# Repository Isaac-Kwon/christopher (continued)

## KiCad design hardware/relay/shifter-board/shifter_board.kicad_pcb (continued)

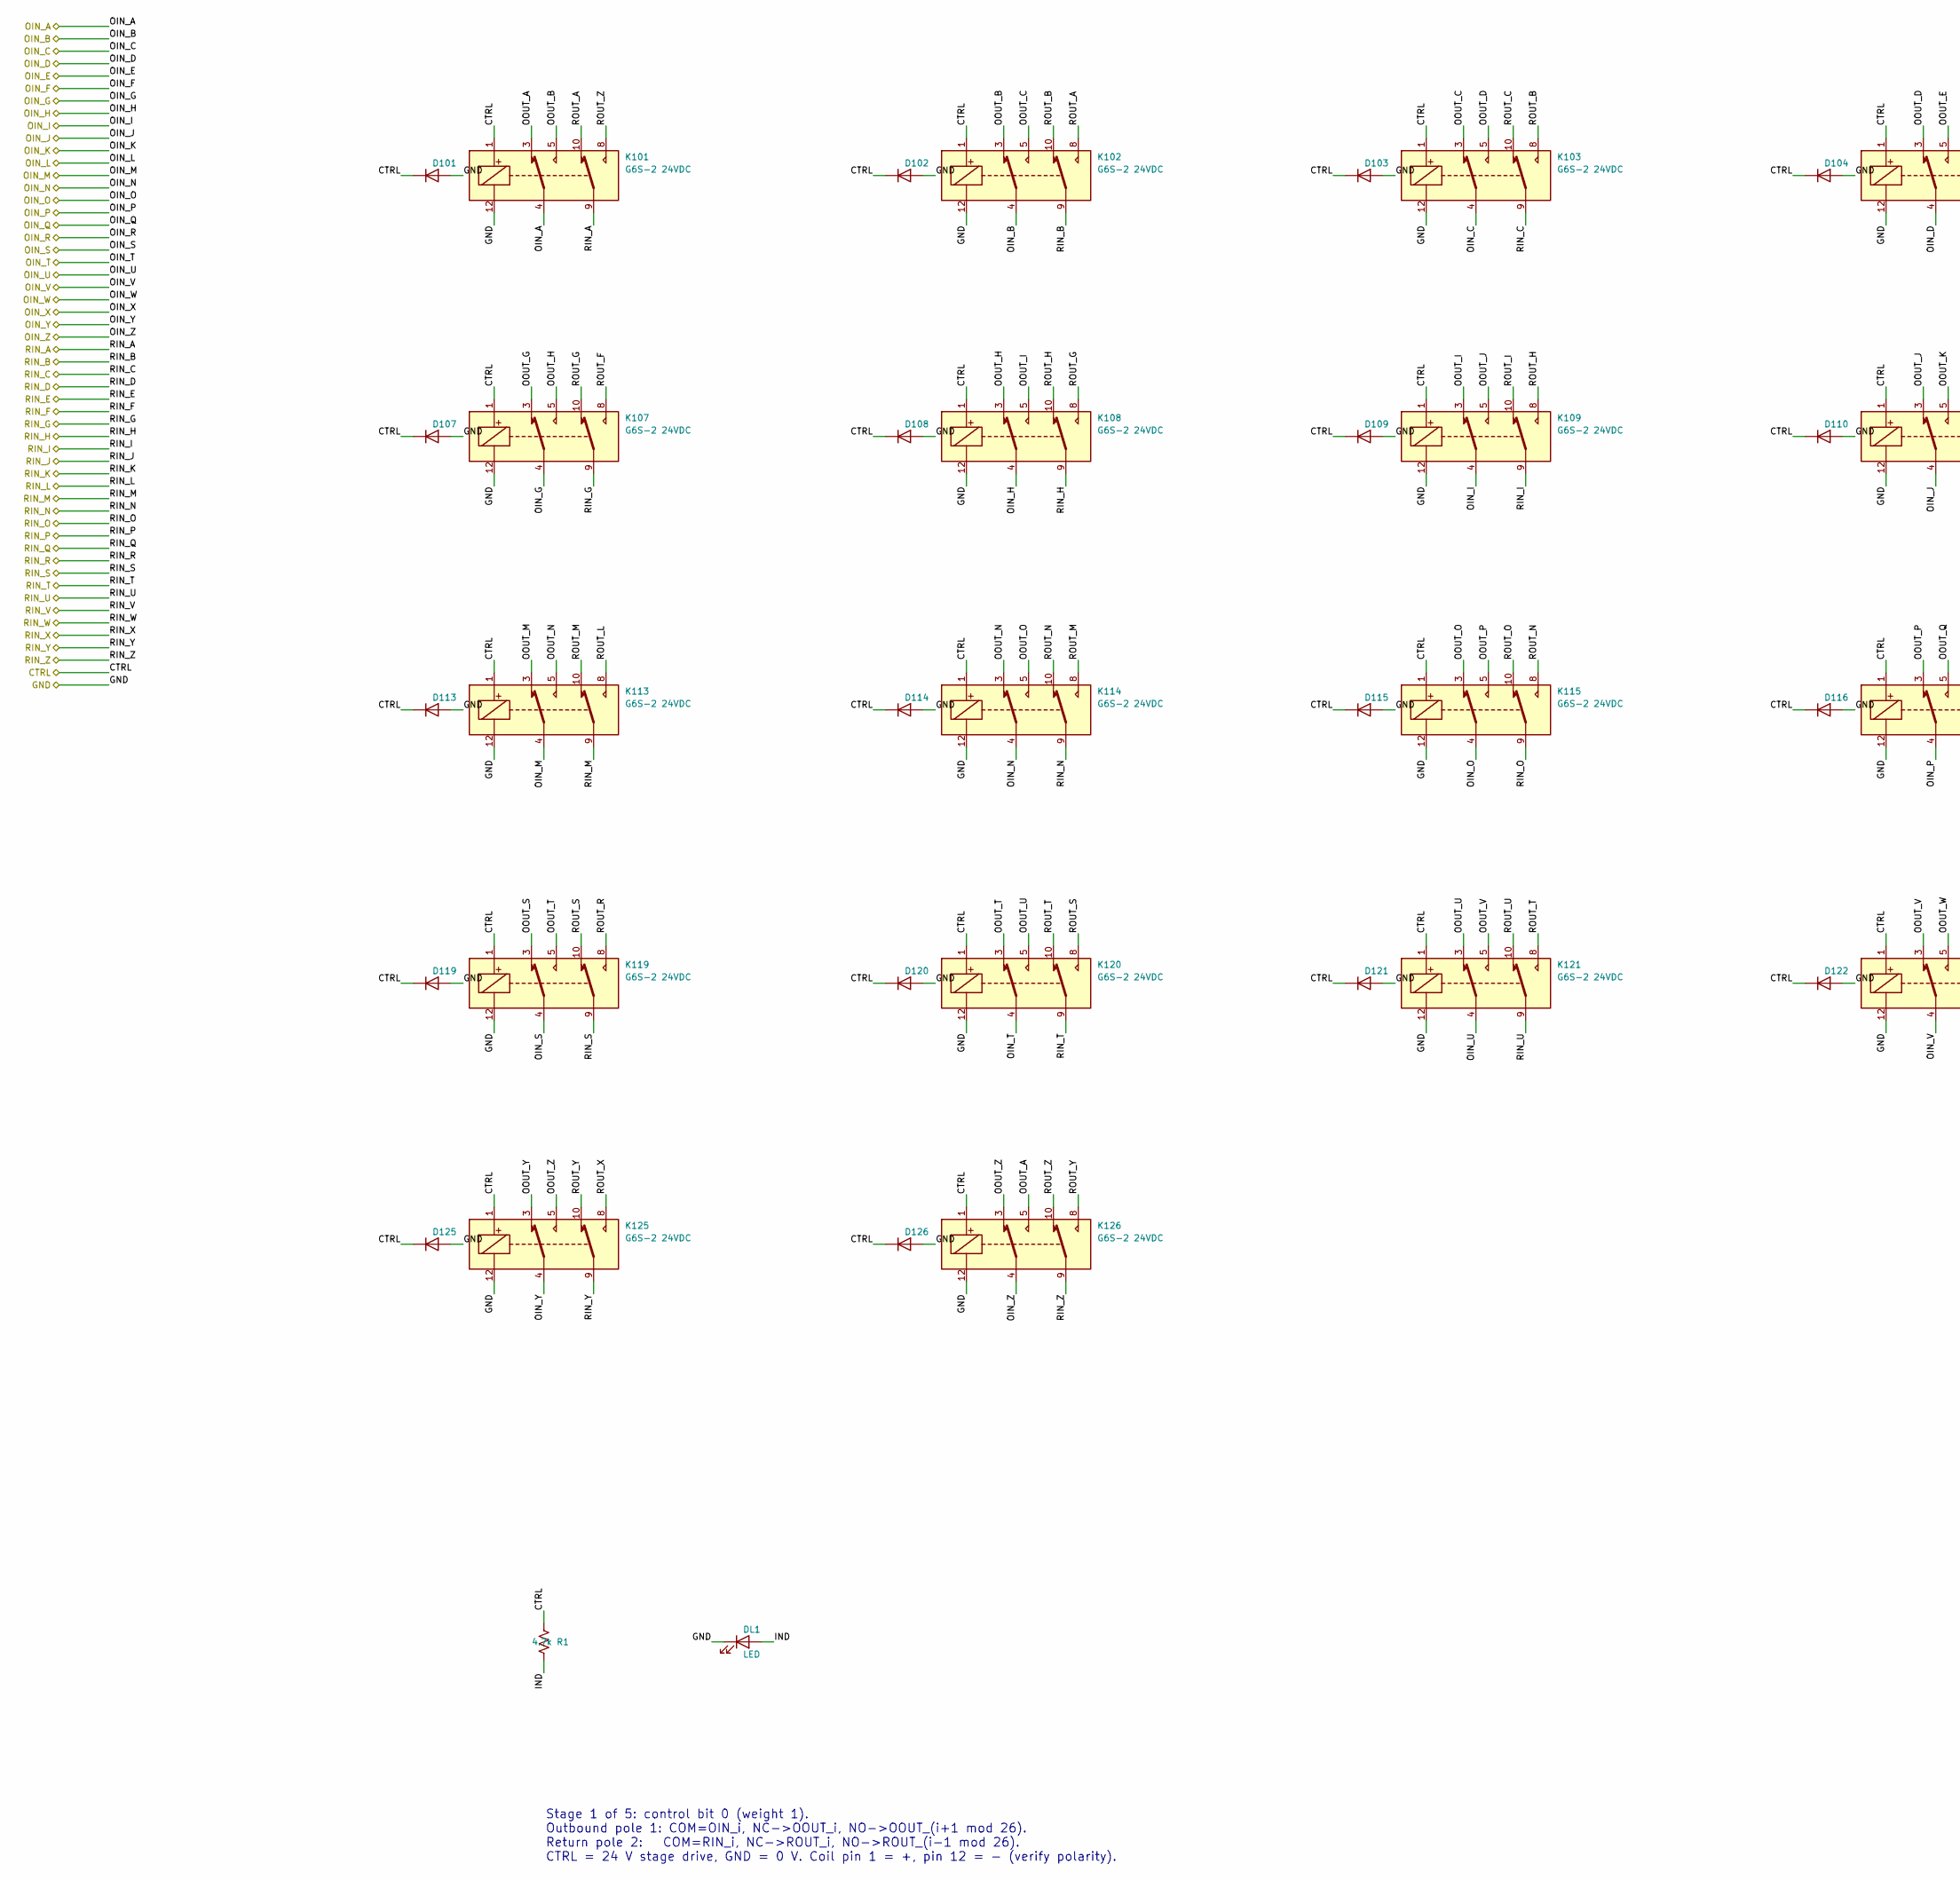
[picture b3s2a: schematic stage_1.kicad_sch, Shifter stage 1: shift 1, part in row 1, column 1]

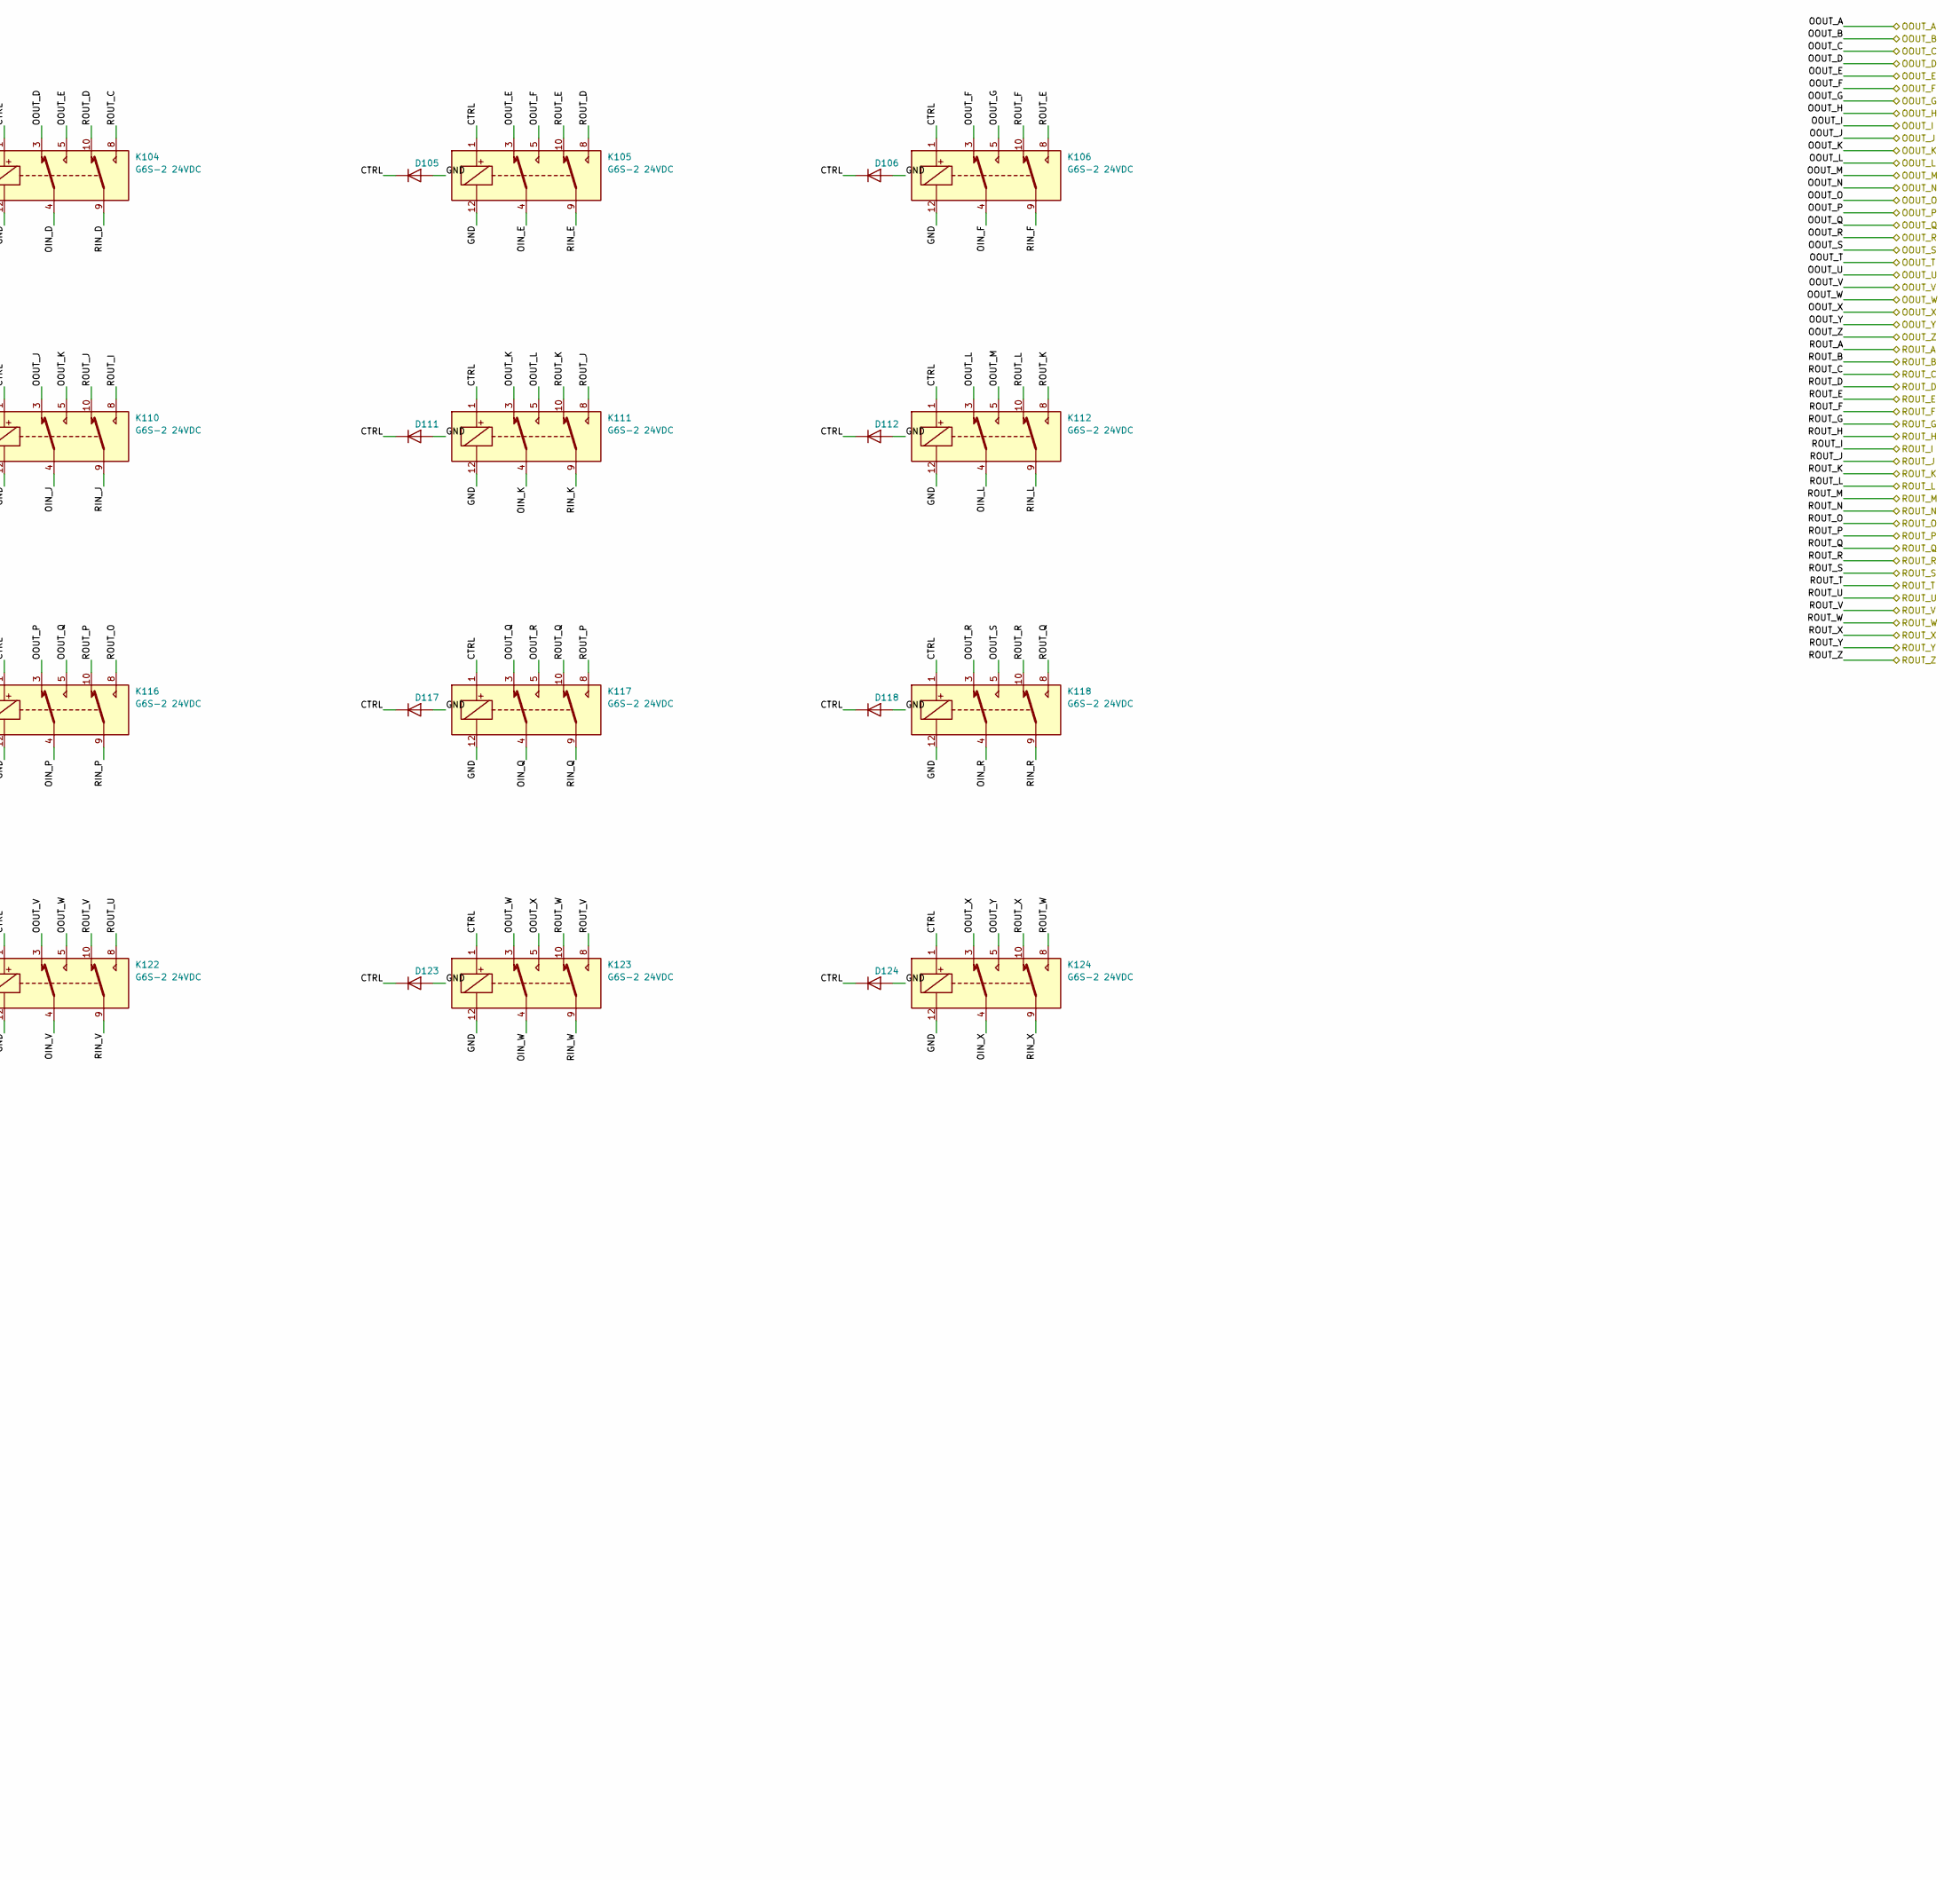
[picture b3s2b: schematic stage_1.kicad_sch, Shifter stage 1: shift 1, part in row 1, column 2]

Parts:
D101, D102, D103, D104, D105, D106, D107, D108, D109, D110, D111, D112, D113, D114, D115, D116, D117, D118, D119, D120, D121, D122, D123, D124, D125, D126: 1N4148W; D_SOD-123
DL1: LED; LED_0603_1608Metric
K101, K102, K103, K104, K105, K106, K107, K108, K109, K110, K111, K112, K113, K114, K115, K116, K117, K118, K119, K120, K121, K122, K123, K124, K125, K126: G6S-2 24VDC; Relay_DPDT_Omron_G6S-2
R1: 4.7k; R_0603_1608Metric

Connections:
/CTRL0: D101.1 (K), D102.1 (K), D103.1 (K), D104.1 (K), D105.1 (K), D106.1 (K), D107.1 (K), D108.1 (K), D109.1 (K), D110.1 (K), D111.1 (K), D112.1 (K), D113.1 (K), D114.1 (K), D115.1 (K), D116.1 (K), D117.1 (K), D118.1 (K), D119.1 (K), D120.1 (K), D121.1 (K), D122.1 (K), D123.1 (K), D124.1 (K), D125.1 (K), D126.1 (K), K101.1, K102.1, K103.1, K104.1, K105.1, K106.1, K107.1, K108.1, K109.1, K110.1, K111.1, K112.1, K113.1, K114.1, K115.1, K116.1, K117.1, K118.1, K119.1, K120.1, K121.1, K122.1, K123.1, K124.1, K125.1, K126.1, R1.1; also elsewhere on the board
/GND: D101.2 (A), D102.2 (A), D103.2 (A), D104.2 (A), D105.2 (A), D106.2 (A), D107.2 (A), D108.2 (A), D109.2 (A), D110.2 (A), D111.2 (A), D112.2 (A), D113.2 (A), D114.2 (A), D115.2 (A), D116.2 (A), D117.2 (A), D118.2 (A), D119.2 (A), D120.2 (A), D121.2 (A), D122.2 (A), D123.2 (A), D124.2 (A), D125.2 (A), D126.2 (A), DL1.1 (K), K101.12, K102.12, K103.12, K104.12, K105.12, K106.12, K107.12, K108.12, K109.12, K110.12, K111.12, K112.12, K113.12, K114.12, K115.12, K116.12, K117.12, K118.12, K119.12, K120.12, K121.12, K122.12, K123.12, K124.12, K125.12, K126.12; also elsewhere on the board
/O1_A: K101.3, K126.5; also elsewhere on the board
/O1_B: K101.5, K102.3; also elsewhere on the board
/O1_C: K102.5, K103.3; also elsewhere on the board
/O1_D: K103.5, K104.3; also elsewhere on the board
/O1_E: K104.5, K105.3; also elsewhere on the board
/O1_F: K105.5, K106.3; also elsewhere on the board
/O1_G: K106.5, K107.3; also elsewhere on the board
/O1_H: K107.5, K108.3; also elsewhere on the board
/O1_I: K108.5, K109.3; also elsewhere on the board
/O1_J: K109.5, K110.3; also elsewhere on the board
/O1_K: K110.5, K111.3; also elsewhere on the board
/O1_L: K111.5, K112.3; also elsewhere on the board
/O1_M: K112.5, K113.3; also elsewhere on the board
/O1_N: K113.5, K114.3; also elsewhere on the board
/O1_O: K114.5, K115.3; also elsewhere on the board
/O1_P: K115.5, K116.3; also elsewhere on the board
/O1_Q: K116.5, K117.3; also elsewhere on the board
/O1_R: K117.5, K118.3; also elsewhere on the board
/O1_S: K118.5, K119.3; also elsewhere on the board
/O1_T: K119.5, K120.3; also elsewhere on the board
/O1_U: K120.5, K121.3; also elsewhere on the board
/O1_V: K121.5, K122.3; also elsewhere on the board
/O1_W: K122.5, K123.3; also elsewhere on the board
/O1_X: K123.5, K124.3; also elsewhere on the board
/O1_Y: K124.5, K125.3; also elsewhere on the board
/O1_Z: K125.5, K126.3; also elsewhere on the board
/OIN_A: K101.4; also elsewhere on the board
/OIN_B: K102.4; also elsewhere on the board
/OIN_C: K103.4; also elsewhere on the board
/OIN_D: K104.4; also elsewhere on the board
/OIN_E: K105.4; also elsewhere on the board
/OIN_F: K106.4; also elsewhere on the board
/OIN_G: K107.4; also elsewhere on the board
/OIN_H: K108.4; also elsewhere on the board
/OIN_I: K109.4; also elsewhere on the board
/OIN_J: K110.4; also elsewhere on the board
/OIN_K: K111.4; also elsewhere on the board
/OIN_L: K112.4; also elsewhere on the board
/OIN_M: K113.4; also elsewhere on the board
/OIN_N: K114.4; also elsewhere on the board
/OIN_O: K115.4; also elsewhere on the board
/OIN_P: K116.4; also elsewhere on the board
/OIN_Q: K117.4; also elsewhere on the board
/OIN_R: K118.4; also elsewhere on the board
/OIN_S: K119.4; also elsewhere on the board
/OIN_T: K120.4; also elsewhere on the board
/OIN_U: K121.4; also elsewhere on the board
/OIN_V: K122.4; also elsewhere on the board
/OIN_W: K123.4; also elsewhere on the board
/OIN_X: K124.4; also elsewhere on the board
/OIN_Y: K125.4; also elsewhere on the board
/OIN_Z: K126.4; also elsewhere on the board
/R1_A: K101.10, K102.8; also elsewhere on the board
/R1_B: K102.10, K103.8; also elsewhere on the board
/R1_C: K103.10, K104.8; also elsewhere on the board
/R1_D: K104.10, K105.8; also elsewhere on the board
/R1_E: K105.10, K106.8; also elsewhere on the board
/R1_F: K106.10, K107.8; also elsewhere on the board
/R1_G: K107.10, K108.8; also elsewhere on the board
/R1_H: K108.10, K109.8; also elsewhere on the board
/R1_I: K109.10, K110.8; also elsewhere on the board
/R1_J: K110.10, K111.8; also elsewhere on the board
/R1_K: K111.10, K112.8; also elsewhere on the board
/R1_L: K112.10, K113.8; also elsewhere on the board
/R1_M: K113.10, K114.8; also elsewhere on the board
/R1_N: K114.10, K115.8; also elsewhere on the board
/R1_O: K115.10, K116.8; also elsewhere on the board
/R1_P: K116.10, K117.8; also elsewhere on the board
/R1_Q: K117.10, K118.8; also elsewhere on the board
/R1_R: K118.10, K119.8; also elsewhere on the board
/R1_S: K119.10, K120.8; also elsewhere on the board
/R1_T: K120.10, K121.8; also elsewhere on the board
/R1_U: K121.10, K122.8; also elsewhere on the board
/R1_V: K122.10, K123.8; also elsewhere on the board
/R1_W: K123.10, K124.8; also elsewhere on the board
/R1_X: K124.10, K125.8; also elsewhere on the board
/R1_Y: K125.10, K126.8; also elsewhere on the board
/R1_Z: K101.8, K126.10; also elsewhere on the board
/RIN_A: K101.9; also elsewhere on the board
/RIN_B: K102.9; also elsewhere on the board
/RIN_C: K103.9; also elsewhere on the board
/RIN_D: K104.9; also elsewhere on the board
/RIN_E: K105.9; also elsewhere on the board
/RIN_F: K106.9; also elsewhere on the board
/RIN_G: K107.9; also elsewhere on the board
/RIN_H: K108.9; also elsewhere on the board
/RIN_I: K109.9; also elsewhere on the board
/RIN_J: K110.9; also elsewhere on the board
/RIN_K: K111.9; also elsewhere on the board
/RIN_L: K112.9; also elsewhere on the board
/RIN_M: K113.9; also elsewhere on the board
/RIN_N: K114.9; also elsewhere on the board
/RIN_O: K115.9; also elsewhere on the board
/RIN_P: K116.9; also elsewhere on the board
/RIN_Q: K117.9; also elsewhere on the board
/RIN_R: K118.9; also elsewhere on the board
/RIN_S: K119.9; also elsewhere on the board
/RIN_T: K120.9; also elsewhere on the board
/RIN_U: K121.9; also elsewhere on the board
/RIN_V: K122.9; also elsewhere on the board
/RIN_W: K123.9; also elsewhere on the board
/RIN_X: K124.9; also elsewhere on the board
/RIN_Y: K125.9; also elsewhere on the board
/RIN_Z: K126.9; also elsewhere on the board
/STAGE_1/IND: DL1.2 (A), R1.2

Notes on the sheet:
Stage 1 of 5: control bit 0 (weight 1). Outbound pole 1: COM=OIN_i, NC->OOUT_i, NO->OOUT_(i+1 mod 26). Return pole 2: COM=RIN_i, NC->ROUT_i, NO->ROUT_(i-1 mod 26). CTRL = 24 V stage drive, GND = 0 V. Coil pin 1 = +, pin 12 = - (verify polarity).

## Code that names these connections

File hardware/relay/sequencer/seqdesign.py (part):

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    "WS": (0, 1), "WJ": (3, 4), "WC": (6, 7, 8), "WK": (7, 8), "HKON": (5, 6, 7, 8), "HLD": (3, 4, 5, 6)}

# relay table: name -> (description, fast_clamp?)   coil net and contacts are in build()
CTRL_PINS = {1: "STROBE", 2: "RUN", 3: "STOPPED", 4: "HOME", 5: "AT_HOME", 6: "END", 22: "ESTOP_A", 23: "ESTOP_RET",
             24: "ILOCK_A", 25: "ILOCK_RET", 34: "JUDGE", 35: "CLEAR", 36: "STOP_LATCH"}
for _k in range(15):
    CTRL_PINS[7 + _k] = f"POS{_k}"
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    d.R(st, "RSL", "RM", "150k", "555 R2 (fixed part)")
    S(st, "POT", "RV", "100k trim", FP["pot"], {"1": "RM", "2": "TH", "3": "TH"}, "Tick trimmer: R2 = 150k + RV1 (set T = 6.3 ms with an oscilloscope)")
    d.C(st, "TH", "GND", "22n C0G", "Timing capacitor (NP0 / C0G: tick tolerance 3 %)")
    d.C(st, "CTL", "GND", "10n", "555 control pin capacitor")
    d.C(st, "V5", "GND", "100n", "555 supply")
    ring = {"3": "Q0", "2": "Q1", "4": "Q2", "7": "Q3", "10": "Q4", "1": "Q5", "5": "Q6", "6": "Q7", "9": "Q8", "11": "Q9",
            "8": "GND", "16": "V5", "14": "CLK", "13": "PARK", "15": "RING_RST"}
    S(st, "4017", "U", "74HC4017", FP["so16"], {**ring, "12": "RING_CO"}, "Decade ring counter: Q0..Q9 one-hot; pin 13 (clock inhibit) = PARK (ring stops in Q9 when no cycle is wanted)",
      nc=("12",), ref="U2")
    d.C(st, "V5", "GND", "100n", "4017 supply")
    d.C(st, "V5", "RING_RST", "100n", "Power-on reset pulse of the ring")
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
    # =========================================================================== INPUT FOLLOWER RELAYS
    si = "inputs"
    for name, pin, coilnet, desc in (("KR", "RUN", "RUN_C", "RUN follower"), ("KSL", "STOP_LATCH", "SL_C", "STOP_LATCH follower"),
                                     ("KHM", "HOME", "HM_C", "HOME follower"), ("KP0", "POS10_IN", "P0_C", "POS10 (r bit 0) follower"),
                                     ("KP3", "POS13_IN", "P3_C", "POS13 (r bit 3) follower"), ("KP4", "POS14_IN", "P4_C", "POS14 (r bit 4) follower"),
                                     ("KOBS", "SPEED_OBS", "OBS_C", "speed selector (observation) follower"),
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    d.PTC(so, "KENB_P", "KENO_B", "PTC 1.1A hold", FP["f1812"], "Bus B clock-rail fuse")
    d.PTC(so, "LOADA_P", "LOAD_A", "PTC 0.1A hold", FP["f1206"], "LOAD bus A fuse")
    d.PTC(so, "LOADB_P", "LOAD_B", "PTC 0.1A hold", FP["f1206"], "LOAD bus B fuse")
    for net, pin, name in (("STROBE_O", "STROBE", "STROBE"), ("JUDGE_O", "JUDGE", "JUDGE"), ("CLEAR_O", "CLEAR", "CLEAR"),
                           ("STP_OUT", "STOPPED", "STOPPED"), ("ATH_OUT", "AT_HOME", "AT_HOME"), ("END_OUT", "END", "END")):
        d.PTC(so, net, pin, "PTC 30mA hold / 100mA trip", FP["f1206"], f"{name} output resettable fuse (hold >= 30 mA, trip <= 100 mA; part not confirmed)")
    for k in range(15):
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    n25.update({"19": "GND", "20": "GND", "21": "GND"})
    S(sc, "DB25", "J", "POS_IN", FP["dsub25"], n25, "POS from the counter common board J4 (1-15 POS0-14, 19-21 0 V); the board passes them through fuses to J2 7-21", nc=("16", "17", "18", "22", "23", "24", "25"), ref="J5")
    S(sc, "DB25", "J", "BUS_TAP", FP["dsub25"], {"3": "A1B", "19": "GND", "20": "GND", "21": "GND"},
      "UNIT_BUS ribbon drop (counter-board J2 layout): only pin 3 (A1B = m carry rail) and the 0 V pins 19-21 are used",
      nc=tuple(str(p) for p in range(1, 26) if p not in (3, 19, 20, 21)), ref="J6")
    S(sc, "T4", "J", "SAFE", FP["t4"], {"1": "ESTOP_SRC", "2": "ESTOP_RET", "3": "ILOCK_SRC", "4": "ILOCK_RET"},
      "Bank-owned safety loops (0003 4.6): 1/2 ESTOP source (power unit F18) / return to K_E; 3/4 ILOCK source (F19) / return to K_I", ref="J7")
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
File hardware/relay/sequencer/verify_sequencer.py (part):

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  STROBE (L8, also after HOME / stop release), CK rise >= CLEAR rise and CK rise + 13 ms <= next STROBE (L9); CK/NCK never both high and
  break-before-make gap below the counters' release time; the register at the contact face (C1-C6, with the random timing-relay
  delays); no missed stop and no false stop; positions tested = 0, 1, 2, ... without repeat or skip across stops, restarts and
  operator RUN toggles; HOME (release, LOAD preset overlapping NCK, no STROBE / JUDGE, exactly one flush CLEAR with L5 and L6 -
  decision 0003 4.4, AT_HOME), END at the 17,576th position or at the slice end, standby (CK = NCK = 0, HOME needed), emergency stop
  (power loss), thermostat; emergency stop in the middle of a cycle with the register's sense relays left latched, then HOME:
  the stop at position 0 must not be missed (stale-K scenario).
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    return sim, b


def home_sequence(sim, b, fails, label="HOME", early_run=None):
    """Press HOME with RUN low; return the (start, park) window of the HOME pass.  early_run = ms after the press at which the
    operator already turns the start switch on (HOME accepted, pass still running): the first STROBE then follows the HOME
    flush CLEAR as early as the relays allow (tightest L6)."""
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    ok = wait_for(sim, lambda: sim.levels_prev.get("AT_HOME", 0) == 1, 1500)
    t1 = sim.t
    if not ok:
        fails.append(f"{label}: AT_HOME never rose")
    elif early_run is not None:
        wait_for(sim, lambda: any(t >= t1 - 30.0 and lv for t, lv in sim.edge_list("STOPPED")), 200, step=1.0)
        park = [t for t, lv in sim.edge_list("STOPPED") if lv and t >= t1 - 30.0]
        if park:
            t1 = park[0]
        else:
            fails.append(f"{label}: ring did not park after the HOME pass")
    else:
        sim.run_until(sim.t + 100)
        if b.n != 0:
            fails.append(f"{label}: counters at {b.n} after HOME")
        if sim.levels_prev.get("END", 0):
            fails.append(f"{label}: END still high after HOME")
        if not sim.levels_prev.get("STOPPED", 0):
            fails.append(f"{label}: STOPPED low although the bank stands at home")
        # the HOME pass ends when the ring parks again (STOPPED rises): the flush CLEAR starts inside [t0, park]
        park = [t for t, lv in sim.edge_list("STOPPED") if lv and t >= t1 - 30.0]
        if park:
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        w = step_window(sim, t0, sim.t)
        got = (w["S"], w["C"], w["CK"])
        if got != (es, ec, eck) or w["J"] != es:
            fails.append(f"step [{tag}] {label}: STROBE/CLEAR/CK = {got}, JUDGE {w['J']}, expected {(es, ec, eck)} "
                         f"(cycles for one press)")
        n_expected_tests += es
        if label.startswith("press into the stop") and not sim.ext.get("STOP_LATCH"):
            fails.append(f"step [{tag}]: no register stop at position 3")
        if es:
            # step cycle at observation speed: ring states Q2..Q8 of this cycle
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        n = nl.net("J2", str(p))
        chk(n is not None and n.startswith("unconnected"), f"J2 pin {p} must be unconnected")
    # no 24 V supply on a signal connector pin other than through a contact + fuse: outputs only via PTC
    for sig, pin in (("STROBE", 1), ("STOPPED", 3), ("AT_HOME", 5), ("END", 6), ("JUDGE", 34), ("CLEAR", 35)):
        fz = [r for r, p in P.items() if r.startswith("F") and nl.net(r, "2") == sig]
        chk(len(fz) == 1, f"{sig}: output fuse missing")
    for k in range(15):
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        users = {r for r, pin in nl.nets[net] if r.startswith("K")}
        chk(len(users) == 1, f"{net} driven by {users}")
    # follower input rules (0003 2.2): pin -> Schottky -> coil, pulldown, clamp on the coil side
    for name, pin in (("KR", "RUN"), ("KSL", "STOP_LATCH"), ("KHM", "HOME"), ("KP0", "POS10_IN"), ("KP3", "POS13_IN"), ("KP4", "POS14_IN")):
        r = ref_of(nl, name)
        coil = nl.net(r, "1")
        ds = [x for x, p in P.items() if x.startswith("D") and "Schottky" in p["value"] and nl.net(x, "2") == pin and nl.net(x, "1") == coil]
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        chk(len(res) == 1, f"{name}: pin pull-down")
    # dial-strip controls (J10, offset-dial README 5): fused switch supply, two follower inputs with the same input rules
    # (a plain flyback diode is a coil-side clamp too: 0003 2.2 allows diode or diode + zener)
    chk(nl.net("J10", "1") == "PANEL_SUP" and nl.net("J10", "2") == "SPEED_OBS" and nl.net("J10", "3") == "STEP", "J10 PANEL pins 1-3")
    n4 = nl.net("J10", "4")
    chk(n4 is not None and n4.startswith("unconnected"), "J10 pin 4 spare (unconnected)")
    chk(any(r.startswith("F") and {nl.net(r, "1"), nl.net(r, "2")} == {"SW", "PANEL_SUP"} for r in P), "J10 switch supply fused")
    for name, pin in (("KOBS", "SPEED_OBS"), ("KSP", "STEP")):
        r = ref_of(nl, name)
        coil = nl.net(r, "1")
        ds = [x for x, p in P.items() if x.startswith("D") and "Schottky" in p["value"] and nl.net(x, "2") == pin and nl.net(x, "1") == coil]
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        chk(len(cl) == 1, f"{name}: flyback clamp on the coil side")
        res = [x for x, p in P.items() if x.startswith("R") and p["value"] == "22k" and {nl.net(x, "1"), nl.net(x, "2")} == {pin, "GND"}]
        chk(len(res) == 1, f"{name}: pin pull-down")
        chk(len(nl.nets[pin]) == 4 and ("J10", "2" if pin == "SPEED_OBS" else "3") in nl.nets[pin],
            f"{pin}: J10 + Schottky + pull-down + lamp resistor only")
    # time base: only a RESISTANCE is switched (README 2.1): R_slow in series with R2, shorted by KOBS NC in series with KSCb NC
    rs = [r for r, p in P.items() if r.startswith("R") and {nl.net(r, "1"), nl.net(r, "2")} == {"DIS", "RSL"}]
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                      ("KC", "CLEAR self-hold through its window")):
        r = ref_of(nl, name)
        chk(nl.net(r, "9") == "WC" and nl.net(r, "8") == "INC", f"{name}: {why} WC -> INC (pole 2 NO)")
    inc_src = {(r, pin) for r, pin in nl.nets["INC"] if r.startswith("K")}
    chk(len(inc_src) == 3, f"INC driven by exactly three contacts, found {sorted(inc_src)}")
    chk(sorted(int(nl.net(d_, "2")[1:]) for d_ in P if d_.startswith("D") and nl.net(d_, "1") == "WC") == [6, 7, 8], "WC window = Q6..Q8")
    # power chain
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    neg_fail = 0
    if not a.no_negative:
        ms = mutants(nl)
        det = 0
        for name, edits in ms:
            m = mutate(nl, edits)
            try:
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
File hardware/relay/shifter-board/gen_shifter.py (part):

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

def g(v: float) -> float:
    """Snap to the 2.54 mm grid (keeps every pin/wire end on the 1.27 mm connection grid)."""
    return round(round(v / 2.54) * 2.54, 2)


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        return x + px, y - py, OUT[a]

    def stub_label(self, px, py, out, name, length=2.54):
        """wire from pin point (screen coords) outward, then a label at the far end."""
        dx, dy = out
        ex, ey = px + dx * length, py - dy * length  # screen y grows downward
        self.wire(px, py, ex, ey)
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    rx, ry = g(140.0), g(360.0)
    sh.symbol(S_R, rx, ry, f"R{st}", "4.7k", FP_R, "", "Stage indicator series resistor", path)
    sh.pin_net(S_R, rx, ry, "1", "CTRL")
    sh.pin_net(S_R, rx, ry, "2", "IND")
    lx = g(rx + 40.0)
    sh.symbol(S_LED, lx, ry, f"DL{st}", "LED", FP_LED, "", f"Stage {st} energised indicator", path)
    sh.pin_net(S_LED, lx, ry, "2", "IND")   # A
    sh.pin_net(S_LED, lx, ry, "1", "GND")   # K
    sh.text(f"Stage {st} of 5: control bit {bit} (weight {shift}).\n"
            f"Outbound pole 1: COM=OIN_i, NC->OOUT_i, NO->OOUT_(i+{shift} mod 26).\n"
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    # control connector
    jx, jy = g(70.0), g(480.0)
    root.symbol(S_DB9, jx, jy, "J5", "CONTROL", FP_DSUB9, "",
                "D-sub 9 pins: 1-5 = CTRL0..CTRL4 (24 V stage drive, weight 1,2,4,8,16), 6-7 = 0 V, 8-9 reserved", path0)
    for b in range(5):
        root.pin_net(S_DB9, jx, jy, str(b + 1), f"CTRL{b}", 5.08)
    for p in ("6", "7"):
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        hx, hy = g(300.0 + 40.0 * k), g(480.0)
        root.symbol(S_HOLE, hx, hy, f"H{k + 1}", "MountingHole_Pad", FP_HOLE, "",
                    "Plated M3 mounting hole, net CHASSIS (metal standoff to the frame / PE)", path0, show_value=False, in_bom=False)
        root.pin_net(S_HOLE, hx, hy, "1", "CHASSIS", 5.08)
    rx, ry = g(480.0), g(480.0)
    root.symbol(S_R, rx, ry, "R6", "1M", FP_R, "", "CHASSIS to 0 V: static drain (DC open-ish)", path0)
    root.pin_net(S_R, rx, ry, "1", "CHASSIS", 5.08)
    root.pin_net(S_R, rx, ry, "2", "GND", 5.08)
    cx, cy = g(540.0), g(480.0)
    root.symbol(S_C, cx, cy, "C1", "10nF 100V", FP_C, "", "CHASSIS to 0 V: ESD / HF path", path0)
    root.pin_net(S_C, cx, cy, "1", "CHASSIS", 5.08)
    root.pin_net(S_C, cx, cy, "2", "GND", 5.08)
    root.text("CHASSIS (decision 0003 7.1): D-sub shells J1-J5 (footprint pads SH) and mounting holes H1-H4 = CHASSIS, not 0 V.\n"
              "R6 1 Mohm || C1 10 nF/100 V between CHASSIS and 0 V (electrostatic path, open for DC).\n"
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
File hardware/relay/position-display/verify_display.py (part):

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  * relay G6S-2: coil 1 (+) / 12 (-); pole 1 = COM 4 / NC 3 / NO 5, pole 2 = COM 9 / NC 10 / NO 8 (as the counter boards);
    a coil is energised iff its pin-1 net is reachable from +24 V through closed contacts, forward diodes (anode 2 ->
    cathode 1) and switched-on P-MOSFET channels; reaching 0 V is a short;
  * input channel: the netlist is traced from each J1 pin through the divider resistor to a BSS138 gate, the BSS138 drain
    through a resistor to an AO3401A gate pulled up to +24 V, and that P-MOSFET's drain (pin functions G/S/D from the
    netlist).  The divider and gate voltages are computed from the resistor values: the N-MOSFET must be off at
    2.4 V and on at 18 V on the pin (decision 0003 2.2), the P-MOSFET Vgs must be <= -4.5 V and >= -12 V over the
    supply range 23.0-26.4 V.  A channel whose analysis fails is reported (no 'maybe' state is simulated);
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                continue
            ups = [(ref, other) for ref, other in self.resistors_at(pin) if other in gate_of_qn]
            if len(ups) != 1:
                errs.append(f"J1 pin {p} ({pin}): {len(ups)} divider resistors to an input MOSFET gate (want 1)")
                continue
            gate = ups[0][1]
            qn = gate_of_qn[gate]
            extra = [ref for ref, other in self.resistors_at(pin) if other not in (gate, self.gnd)]
            extra += [ref for ref, other in self.resistors_at(gate) if other not in (pin, self.gnd)]
            if extra:
                errs.append(f"J1 pin {p}: unexpected resistors on the input / gate nets: {extra}")
            g_in = sum(1 / r for r in self.resistors_between(pin, gate))
            g_gnd = sum(1 / r for r in self.resistors_between(gate, self.gnd))
            g_pd = sum(1 / r for r in self.resistors_between(pin, self.gnd))
            if not g_gnd or not g_pd:
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            a = dict(ratio=ratio, req=1 / g_eq, off=2.4 * ratio, on=18.0 * ratio, gmax=V_MAX * ratio, vgs=vgs,
                     i_nom=V_NOM * g_eq, i_max=V_MAX * g_eq, qn=qn, qp=qp)
            if a["off"] > QN_OFF_MAX:
                errs.append(f"J1 pin {p}: gate {a['off']:.2f} V at 2.4 V input (must be <= {QN_OFF_MAX} V: off)")
            if a["on"] < QN_ON_MIN:
                errs.append(f"J1 pin {p}: gate {a['on']:.2f} V at 18 V input (must be >= {QN_ON_MIN} V: on)")
            if a["gmax"] > 20:
                errs.append(f"J1 pin {p}: gate over 20 V")
            if max(vgs) > QP_VGS_ON or min(vgs) < QP_VGS_ABS:
                errs.append(f"{qp}: Vgs {vgs[0]:.2f}..{vgs[1]:.2f} V outside [{QP_VGS_ABS}, {QP_VGS_ON}]")
            ch[p] = (self.fn_pin(qp, "D"), a)
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NEGATIVE = [
    ("tree: digit m bit 1 contact NC/NO swapped (K210 pins 3<->5)", lambda nl: swap_node(nl, "K210", "3", "5")),
    ("tree: digit r bit 4 pole 2 NC/NO swapped (K344 pins 10<->8)", lambda nl: swap_node(nl, "K344", "10", "8")),
    ("connector: POS0 / POS1 swapped (J1 pins 1<->2)", lambda nl: swap_node(nl, "J1", "1", "2")),
    ("connector: l bit 4 / m bit 0 swapped (J1 pins 5<->6)", lambda nl: swap_node(nl, "J1", "5", "6")),
    ("lamps: digit l lamps F and G exchanged (DS105 / DS106 anodes)", lambda nl: _swap_two(nl, ("DS105", "2"), ("DS106", "2"))),
    ("coil: a digit-l bit-3 relay on the bit-4 coil bus (K130.1 -> net of K140.1)", lambda nl: move_node(nl, ("K130", "1"), ("K140", "1"))),
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    bus_of = {p: drain for p, (drain, _x) in ch.items()}
    counts = [len(per_bus.get(bus_of[p], [])) for p in range(1, 16)]
    print(f"structure: {n_rel} relays (G6S-2; relays per POS line 1-15 = {counts}), "
          f"39 flyback diodes, 78 lamps with letter values A-Z x 3, power input chain, CHASSIS, J1 = counter J4 pin layout: OK")
    a0 = ch[1][1]
    print(f"receivers (from the netlist values): gate = {a0['ratio']:.3f} x pin voltage -> {a0['off']:.2f} V at 2.4 V (off, BSS138 "
          f"Vth >= {VTH_N[0]} V), {a0['on']:.2f} V at 18 V (on, Vth <= {VTH_N[1]} V), {a0['gmax']:.2f} V at 26.4 V; "
          f"P-MOSFET Vgs {a0['vgs'][0]:.2f} .. {a0['vgs'][1]:.2f} V; equivalent load {a0['req'] / 1e3:.1f} kOhm = "
          f"{a0['i_nom'] * 1e3:.2f} mA at 24 V, {a0['i_max'] * 1e3:.2f} mA at 26.4 V (all 15 channels identical: "
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        seq = seq_follower_current(v)
        tot3, tot = seq + MONITOR_MAX + disp, MONITOR_MAX + disp
        worst = max(worst, tot3)
        print(f"POS load per pin at {v:.1f} V: POS10/13/14 = sequencer follower {seq * 1e3:.2f} + monitor (0003 max) "
              f"{MONITOR_MAX * 1e3:.1f} + display {disp * 1e3:.2f} = {tot3 * 1e3:.2f} mA; other pins = {tot * 1e3:.2f} mA "
              f"(limit {POS_BUDGET * 1e3:.0f} mA)")
    if worst > POS_BUDGET:
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
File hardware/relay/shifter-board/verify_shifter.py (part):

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        if net_of(d, "1") != net_of("J5", str(b + 1)) or net_of(d, "2") != gnd:
            errs.append(f"{d}: flyback diode is not across its coil net")

    # --- 0003 S1/S2: pins 27-29 of J1-J4 float, CHASSIS is separate from 0 V and joined only by R6 || C1
    for ref in ("J1", "J2", "J3", "J4"):
        for p in ("27", "28", "29"):
            n = net_of(ref, p)
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                    bad += 1
                    gs = sorted(f"{r}.{p}" for r, p in got) or ["(open)"]
                    errs.append(f"a={a:2d} {what} {src}.{i + 1} -> {gs}, expected {dst}.{want + 1}")
        # CHASSIS must not touch any signal pin or the control pins in any control state
        if chassis is not None and uf.find(nl.nets[chassis][0]) in ({uf.find(p) for p in all_sig} |
                                                                     {uf.find(("J5", str(b + 1))) for b in range(BITS)}):
            errs.append(f"a={a}: CHASSIS is connected to a signal or control pin")
        # control pins must stay isolated from the signal pins (checked once, a-independent)
        for b in range(BITS):
            if uf.find(("J5", str(b + 1))) in {uf.find(p) for p in all_sig}:
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    return [
        ("J1 pin 27 tied to 0 V (reference pin not left open)", add_node(nl, gnd, ("J1", "27"))),
        ("J4 pin 29 tied to 0 V", add_node(nl, gnd, ("J4", "29"))),
        ("J5 shell-side: 0 V pin 6 shorted onto CHASSIS", add_node(nl, chassis, ("J5", "6"))),
        ("mounting hole H3 left off CHASSIS (moved to 0 V)", add_node(nl, gnd, ("H3", "1"))),
        ("R6 (1M) moved off 0 V onto CHASSIS", add_node(nl, chassis, ("R6", "2"))),
    ]
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    ("swap two outbound IN lines (J1 pins 1<->2)", "J1", "1", "2"),
    ("swap two return OUT lines (J4 pins 20<->25)", "J4", "20", "25"),
    ("swap NC/NO of stage-3 relay K305 pole 1 (pins 3<->5)", "K305", "3", "5"),
    ("swap control bits CTRL1<->CTRL2 (J5 pins 2<->3)", "J5", "2", "3"),
]


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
